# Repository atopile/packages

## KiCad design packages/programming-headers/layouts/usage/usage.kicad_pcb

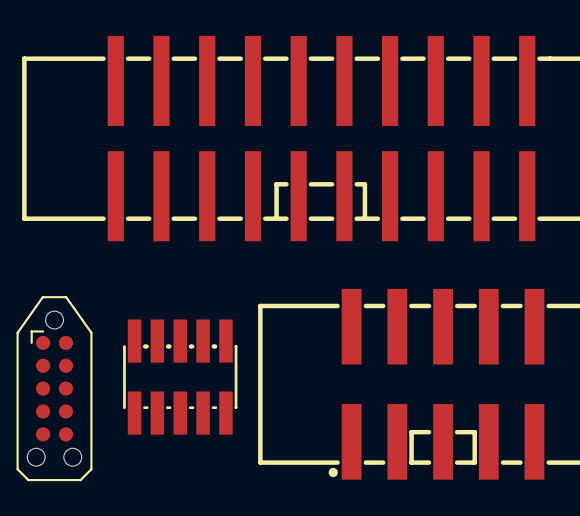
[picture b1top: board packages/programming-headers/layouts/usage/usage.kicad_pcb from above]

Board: 2 copper layers, 4 parts (0 on the bottom side), 4 nets, no tracks yet.

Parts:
CN1: IDC-SMD_10P-P2.54-V-R2-C5-S9.50
CN2: CONN-SMD_20P-P2.54_BH-00019
J2: Tag-Connect_TC2050-IDC-NL_2x05_P1.27mm_Vertical
U1: HDR-SMD_10P-P1.27-V-M-R2-C5-LS5.3

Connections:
idc_2_54mm_10pin_arm_cortex-swd-lv: CN1.3, CN1.5, CN1.9
jtag-lv: CN2.4, CN2.6, CN2.8, CN2.10, CN2.12, CN2.14, CN2.16, CN2.18, CN2.20
lv: U1.3, U1.5, U1.9
tc2050_arm_cortex-swd-lv: J2.3, J2.5

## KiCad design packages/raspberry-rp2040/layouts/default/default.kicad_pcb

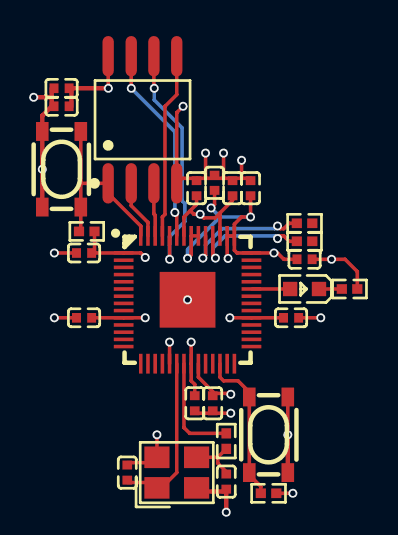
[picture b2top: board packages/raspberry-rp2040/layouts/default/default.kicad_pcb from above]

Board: 4 copper layers, 26 parts (0 on the bottom side), 18 nets.

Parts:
C2, C8, C15: 2.2µF; C0402
C3, C4, C9, C10, C11, C12, C13, C14, C16: 100nF; C0402
C5, C6: 15pF; C0402
LED1: LED0603-RD
R1, R3, R4: 10kΩ; R0402
R2: 1kΩ; R0402
R5, R6: 27Ω; R0402
SW1, SW2: KEY-SMD_4P-L4.2-W3.2-P2.20-LS4.6
U1: LQFN-56_L7.0-W7.0-P0.4-EP
U2: SOIC-8_L5.3-W5.3-P1.27-LS8.0-BL
X1: CRYSTAL-SMD_4P-L3.2-W2.5-BL

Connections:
A: LED1.2, U1.37
CHIP_SELECT: R1.1, SW1.1, SW1.2, U1.56, U2.1
CLOCK: U1.52, U2.6
DATA_0: U1.53, U2.5
DATA_1: U1.55, U2.2
DATA_2: U1.54, U2.3
DATA_3: U1.51, U2.7
DATA_N: R6.2, U1.46
DATA_P: R5.2, U1.47
K: LED1.1, R3.2
RUN: R4.1, SW2.1, SW2.2, U1.26
XIN: C5.1, U1.20, X1.1
XOUT: R2.2, U1.21
compensation_capacitors[1]-power-hv: C6.1, R2.1, X1.3
core_power_decoupling_capacitor[2]-power-hv: C2.1, C3.1, C4.1, U1.23, U1.45, U1.50
hv: C8.1, C9.1, C10.1, C11.1, C12.1, C13.1, C14.1, C15.1, C16.1, R1.2, R4.2, U1.1, U1.10, U1.22, U1.33, U1.42, U1.43, U1.44, U1.48, U1.49, U2.8
lv: C8.2, C9.2, C10.2, C11.2, C12.2, C13.2, C14.2, C15.2, C16.2, R3.1, SW1.3, SW1.4, SW2.3, SW2.4, U1.19, U1.57, U2.4
power-lv: C2.2, C3.2, C4.2, C5.2, C6.2, X1.2, X1.4

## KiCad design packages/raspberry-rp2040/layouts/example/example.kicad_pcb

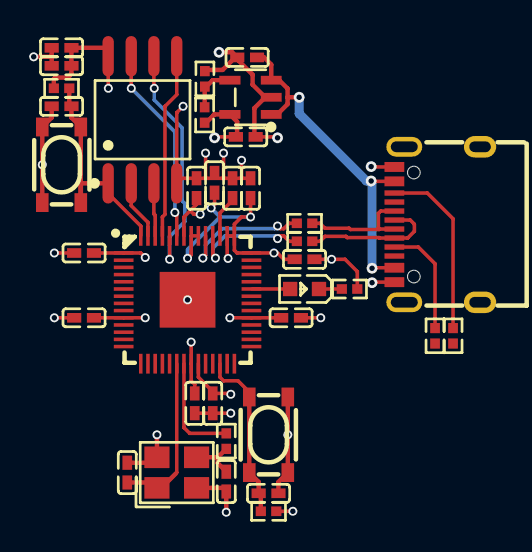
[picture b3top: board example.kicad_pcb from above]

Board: 4 copper layers, 36 parts (0 on the bottom side), 23 nets.

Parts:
C1, C2, C3, C18: 1µF ±10% 25V X5R; C0402
C4, C9, C16: 2.2µF ±20% 6.3V X5R; C0402
C5, C6, C10, C11, C12, C13, C14, C15, C17: 100nF ±10% 16V X7R; C0402
C7, C8: 15pF ±5% 50V C0G; C0402
LED1: LED0603-RD
R1: 5.1kΩ ±1% 62.5mW; R0402
R2, R3, R5, R6: 10kΩ ±1% 62.5mW; R0402
R4: 1kΩ ±1% 62.5mW; R0402
R7, R8: 27Ω ±1% 62.5mW; R0402
R9, R10: 51kΩ ±1% 62.5mW; R0402
SW1, SW2: KEY-SMD_4P-L4.2-W3.2-P2.20-LS4.6
U1: SOT-23-5_L3.0-W1.7-P0.95-LS2.8-BL
U2: LQFN-56_L7.0-W7.0-P0.4-EP
U3: SOIC-8_L5.3-W5.3-P1.27-LS8.0-BL
USB1: USB-C-SMD_TYPE-C-6PIN-2MD-073
X1: CRYSTAL-SMD_4P-L3.2-W2.5-BL

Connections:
3V3: C2.1, C9.1, C10.1, C11.1, C12.1, C13.1, C14.1, C15.1, C16.1, C17.1, R2.1, R3.1, R6.1, U1.5, U2.1, U2.10, U2.22, U2.33, U2.42, U2.43, U2.44, U2.48, U2.49, U3.8
A: LED1.2, U2.37
ADJ_NC: R1.1, R2.2, U1.4
CC1: R9.2, USB1.4
CC2: R10.2, USB1.10
DI: U2.53, U3.5
DO: U2.55, U3.2
DVDD: C4.1, C5.1, C6.1, U2.23, U2.45, U2.50
K: LED1.1, R5.2
QSPI_SCLK: U2.52, U3.6
QSPI_SD2: U2.54, U3.3
QSPI_SD3: U2.51, U3.7
QSPI_SS: C3.1, R3.2, SW1.3, SW1.4, U2.56, U3.1
RP_USB_N: R8.2, U2.46
RP_USB_P: R7.2, U2.47
RUN: C18.1, R6.2, SW2.3, SW2.4, U2.26
USB_N: R8.1, USB1.5, USB1.7
USB_P: R7.1, USB1.6, USB1.8
gnd: C1.2, C2.2, C3.2, C4.2, C5.2, C6.2, C7.2, C8.2, C9.2, C10.2, C11.2, C12.2, C13.2, C14.2, C15.2, C16.2, C17.2, C18.2, R1.2, R5.1, R9.1, R10.1, SW1.1, SW1.2, SW2.1, SW2.2, U1.2, U2.57, U3.4, USB1.1, USB1.12, USB1.13, USB1.14, X1.2, X1.4
hv: C1.1, U1.1, U1.3, USB1.2, USB1.11
output: C8.1, R4.1, X1.3
xin: C7.1, U2.20, X1.1
xout: R4.2, U2.21

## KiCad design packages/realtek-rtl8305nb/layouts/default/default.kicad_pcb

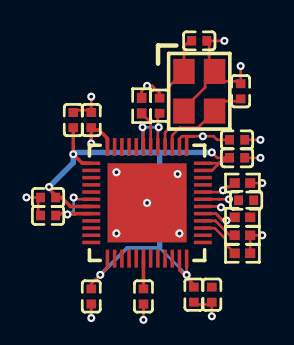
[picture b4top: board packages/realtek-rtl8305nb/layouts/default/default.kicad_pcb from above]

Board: 2 copper layers, 21 parts (0 on the bottom side), 10 nets.

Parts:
C1, C2, C3, C4, C5, C6, C7, C8, C9, C10, C11, C12, C13, C14: 0F; C0402
R1: 2490Ω; R0402
R2, R3, R5: 10000Ω; R0402
R4: 100000Ω; R0402
U1: QFN-48_L6.0-W6.0-P0.40-TL-EP4.4
X1: OSC-SMD_4P-L3.2-W2.5-BL_SIT8008BI

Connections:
ETH_LED_LINK: R4.1, U1.29
IBREF: R1.1, U1.42
LDIND_DIS_LD: R3.1, U1.28
RESETB: R2.1, U1.27
crystal_caps[0]-power-hv: U1.40, X1.1
crystal_caps[1]-power-hv: U1.39, X1.3
decoupling_3v3[5]-power-hv: R2.2, R3.2, R5.2, U1.6, U1.8, U1.18, U1.31, U1.37, U1.38, U1.48
ethernets[2]-ETH_LED_LINK: R5.1, U1.32
hv: U1.1, U1.7, U1.13, U1.23, U1.24, U1.35, U1.36, U1.41, U1.43
lv: R1.2, R4.2, U1.49, X1.2, X1.4

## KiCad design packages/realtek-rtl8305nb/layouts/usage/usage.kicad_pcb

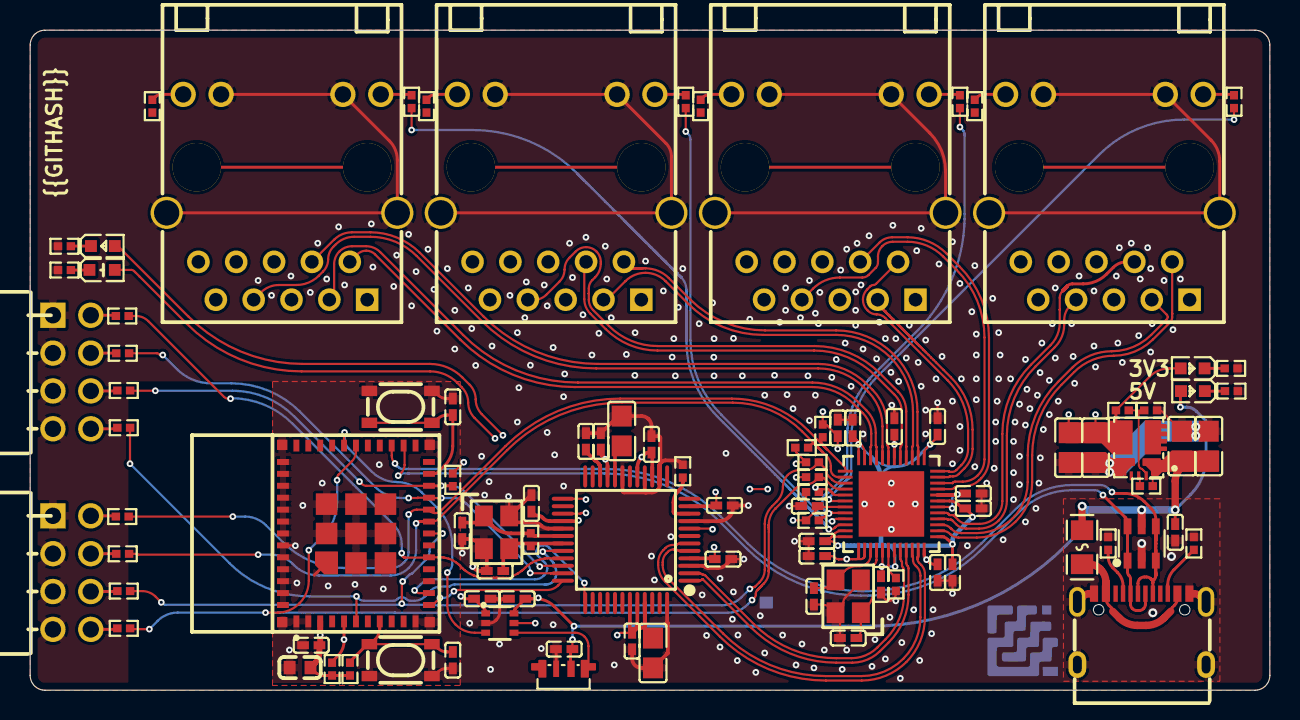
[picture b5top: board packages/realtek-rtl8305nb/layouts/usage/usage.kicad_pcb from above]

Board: 4 copper layers, 83.2 x 44.3 mm, 98 parts (1 on the bottom side), 80 nets.

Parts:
C1, C2, C4, C7, C8, C9, C12, C13, C14, C15, C16, C17, C18, C19, C20, C21, C22, C23, C24, C26, C27, C28, C29, C30, C31: 100nF ±10% 16V X7R; C0402
C3: 22µF ±20% 6.3V X5R; C0603
C5, C6: 10µF ±10% 25V X7R; C0805
C10, C11, C34, C35: 18pF ±5% 50V C0G; C0402
C25: 10µF ±10% 10V X5R; C0805
C32: 10nF ±10% 50V X7R; C0402
C33: 4.7µF ±10% 10V X7R; C0805
C36, C37: 22µF ±20% 10V X7R; C0805
D1: SOT-23-6_L2.9-W1.6-P0.95-LS2.8-BL
F1: F0805
LED1: LED0603-R-RD
LED2, LED3, LED4: LED0603-RD
LOGO1: atopile_Logo_25x6mm
R1, R2, R3, R4, R5, R6, R7, R8: 1kΩ ±1% 62.5mW; R0402
R9, R10, R11, R22, R25, R27, R28, R33, R34, R35, R36, R37: 10kΩ ±1% 62.5mW; R0402
R12, R13, R14, R15, R16, R17, R18, R19: 470Ω ±1% 62.5mW; R0402
R20, R21: 4.7kΩ ±1% 62.5mW; R0402
R23: 2.2kΩ ±1% 62.5mW; R0402
R24: 2.49kΩ ±1% 62.5mW; R0402
R26: 100kΩ ±1% 62.5mW; R0402
R29, R30: 5.1kΩ ±1% 62.5mW; R0402
R31: 12.4kΩ ±1% 62.5mW; R0402
R32: 1MΩ ±1% 62.5mW; R0402
RJ1, RJ2, RJ3, RJ4: RJ45-TH_HR911130A
SW1, SW2: KEY-SMD_4P-L4.2-W3.2-P2.20-LS4.6
U1: WIFIM-SMD_ESP32-C3-MINI-1
U2: QFN-48_L6.0-W6.0-P0.40-TL-EP4.4
U3: LQFP-48_L7.0-W7.0-P0.50-LS9.0-BL
U4: QFN-7_L4.0-W3.3_TPSM863257RDXR
U5: LED-SMD_4P-L3.5-W1.6_SK6805SIDE-G-001
U6, U7: HDR-TH_8P-P2.54-H-F-R2-C4-W8.5
U8: SC-70-6_L2.2-W1.3-P0.65-LS2.1-BR
USB1: USB-C-SMD_TYPE-C-6PIN-2MD-073
X1, X2: OSC-SMD_4P-L3.2-W2.5-BL_SIT8008BI

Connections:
+3V3: C3.1, C4.1, C7.1, C18.1, C19.1, C20.1, C21.1, C22.1, C23.1, C25.1, C26.1, C27.1, C28.1, C29.1, C30.1, C31.1, C36.1, C37.1, LED3.2, R9.2, R10.2, R11.1, R20.2, R21.2, R25.2, R27.2, R28.2, R33.1, U1.3, U2.6, U2.8, U2.18, U2.31, U2.37, U2.38, U2.48, U3.4, U3.8, U3.11, U3.15, U3.17, U3.21, U3.28, U3.43, U3.44, U3.45, U4.3, U8.1, U8.5
+5V: C5.1, C6.1, C8.1, C9.1, C24.1, D1.5, F1.2, LED4.2, R22.1, U4.1, U5.3, U8.6
B: U5.4, U8.4
EN: R22.2, U4.6
EXRES1: R31.1, U3.10
GND: C1.1, C2.1, C3.2, C4.2, C5.2, C6.2, C7.2, C8.2, C9.2, C10.2, C11.2, C12.2, C13.2, C14.2, C15.2, C16.2, C17.2, C18.2, C19.2, C20.2, C21.2, C22.2, C23.2, C24.2, C25.2, C26.2, C27.2, C28.2, C29.2, C30.2, C31.2, C32.2, C33.2, C34.2, C35.2, C36.2, C37.2, D1.2, R23.2, R24.2, R26.2, R29.2, R30.2, R31.2, R34.2, R35.2, R36.2, R37.2, RJ1.12, RJ1.13, RJ1.SHIELD0, RJ1.SHIELD1, RJ2.12, RJ2.13, RJ2.SHIELD0, RJ2.SHIELD1, RJ3.12, RJ3.13, RJ3.SHIELD0, RJ3.SHIELD1, RJ4.12, RJ4.13, RJ4.SHIELD0, RJ4.SHIELD1, SW1.1, SW1.2, SW2.1, SW2.2, U1.1, U1.2, U1.11, U1.14, U1.36, U1.37, U1.38, U1.39, U1.40, U1.41, U1.42, U1.43, U1.44, U1.45, U1.46, U1.47, U1.48, U1.49, U1.50, U1.51, U1.52, U1.53, U2.49, U3.3, U3.9, U3.14, U3.16, U3.19, U3.29, U3.48, U4.4, U5.2, U6.1, U6.3, U6.5, U6.7, U7.1, U7.3, U7.5, U7.7, U8.2, USB1.1, USB1.12, USB1.13, USB1.14, USB1.15, USB1.16, X1.2, X1.4, X2.2, X2.4
I2C_SCL: R5.1, R20.1, U1.20, U2.25
I2C_SDA: R6.1, R21.1, U1.19, U2.26
IBREF: R24.1, U2.42
N_TRST: C2.2, R11.2, SW2.3, SW2.4, U1.8
P1V2O: C32.1, U3.22
RX: R8.1, R25.1, U1.30, U2.28
SPI_CS: R4.1, U1.6, U3.32
SPI_MISO: R3.1, R10.1, U1.22, U3.34
SPI_MOSI: R2.1, U1.21, U3.35
SPI_SCLK: R1.1, U1.16, U3.33
TOCAP: C33.1, U3.20
TX: U1.31, U8.3
USB_D_N: D1.1, D1.6, U1.26, USB1.5, USB1.7
USB_D_P: D1.3, D1.4, U1.27, USB1.6, USB1.8
VDIV_OUTPUT: R23.1, R33.2, U4.7
W5500_INT: U1.12, U3.36
W5500_RST: U1.13, U3.37
XI: C10.1, U2.40, X1.1
XI_CLKIN: C34.1, R32.1, U3.30, X2.1
_power_1v2-VCC: C12.1, C13.1, C14.1, C15.1, C16.1, C17.1, U2.1, U2.7, U2.13, U2.23, U2.24, U2.35, U2.36, U2.41, U2.43
activity_led-cathode: LED1.2, R34.1
activity_led-power-anode: LED1.1, U3.27
cc[0]-line: R29.1, USB1.4
cc[1]-line: R30.1, USB1.10
crystal-XO-0: C11.1, U2.39, X1.3
crystal-XO-1: C35.1, R32.2, U3.31, X2.3
data_1: R9.1, U1.5
data_3: R7.1, R28.1, U1.18, U2.27
debug_header-_2-0: R1.2, U6.2
debug_header-_2-1: R5.2, U7.2
debug_header-_4-0: R2.2, U6.4
debug_header-_4-1: R6.2, U7.4
debug_header-_6-0: R3.2, U6.6
debug_header-_6-1: R7.2, U7.6
debug_header-_8-0: R4.2, U6.8
debug_header-_8-1: R8.2, U7.8
ethernet-ETH_P0_N: U2.45, U3.1
ethernet-ETH_P0_P: U2.44, U3.2
ethernet-ETH_P1_N: U2.46, U3.5
ethernet-ETH_P1_P: U2.47, U3.6
ethernet_ports[0]-_11: R13.2, RJ1.11
ethernet_ports[0]-_14: R12.2, RJ1.14
ethernet_ports[1]-_11: R15.2, RJ2.11
ethernet_ports[1]-_14: R14.2, RJ2.14
ethernet_ports[2]-_11: R17.2, RJ3.11
ethernet_ports[2]-_14: R16.2, RJ3.14
ethernet_ports[3]-_11: R19.2, RJ4.11
ethernet_ports[3]-_14: R18.2, RJ4.14
ethernets[1]-ETH_LED_LINK: R13.1, U2.30
ethernets[1]-ETH_P0_N: RJ1.P3, U2.3
ethernets[1]-ETH_P0_P: RJ1.P2, U2.2
ethernets[1]-ETH_P1_N: RJ1.P7, U2.4
ethernets[1]-ETH_P1_P: RJ1.P4, U2.5
ethernets[2]-ETH_LED_LINK: R15.1, R27.1, U2.32
ethernets[2]-ETH_P0_N: RJ2.P3, U2.11
ethernets[2]-ETH_P0_P: RJ2.P2, U2.12
ethernets[2]-ETH_P1_N: RJ2.P7, U2.10
ethernets[2]-ETH_P1_P: RJ2.P4, U2.9
ethernets[3]-ETH_LED_LINK: R17.1, U2.33
ethernets[3]-ETH_P0_N: RJ3.P3, U2.15
ethernets[3]-ETH_P0_P: RJ3.P2, U2.14
ethernets[3]-ETH_P1_N: RJ3.P7, U2.16
ethernets[3]-ETH_P1_P: RJ3.P4, U2.17
ethernets[4]-ETH_LED_LINK: R19.1, U2.34
ethernets[4]-ETH_P0_N: RJ4.P3, U2.21
ethernets[4]-ETH_P0_P: RJ4.P2, U2.22
ethernets[4]-ETH_P1_N: RJ4.P7, U2.20
ethernets[4]-ETH_P1_P: RJ4.P4, U2.19
footprint-cathode-0: LED2.1, R35.1
footprint-cathode-1: LED3.1, R36.1
footprint-cathode-2: LED4.1, R37.1
link_led-power-anode: LED2.2, R26.1, U2.29, U3.25
output: C1.2, SW1.3, SW1.4, U1.23
power_vbus-VCC: F1.1, USB1.2, USB1.11

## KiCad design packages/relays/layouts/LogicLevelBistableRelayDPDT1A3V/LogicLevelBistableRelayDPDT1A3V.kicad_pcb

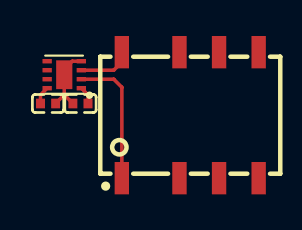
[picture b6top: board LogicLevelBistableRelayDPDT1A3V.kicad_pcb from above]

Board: 2 copper layers, 4 parts (0 on the bottom side), 5 nets.

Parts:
C1, C2: 0F; C0402
U1: WSON-8_L2.0-W2.0-P0.50-TL-EP
U2: RELAY-SMD_G6KU-2F-Y

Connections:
hv: C1.1, U1.8
lv: C1.2, C2.2, U1.4, U1.9
motor_outs[0]: U1.2, U2.1
motor_outs[1]: U1.3, U2.8
motor_power_decoupling_capacitor-power-hv: C2.1, U1.1
